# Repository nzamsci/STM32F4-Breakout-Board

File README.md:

# STM32F405RGT6 Microcontroller Breakout Board
[UNFINISHED] PCB Design based around the STM32F405RGT6 microcontroller. Design includes a 20-pin J-Link debug adapter (SWD), I2C, SPI, and USART interfaces, and a 16 MHz external oscillator.

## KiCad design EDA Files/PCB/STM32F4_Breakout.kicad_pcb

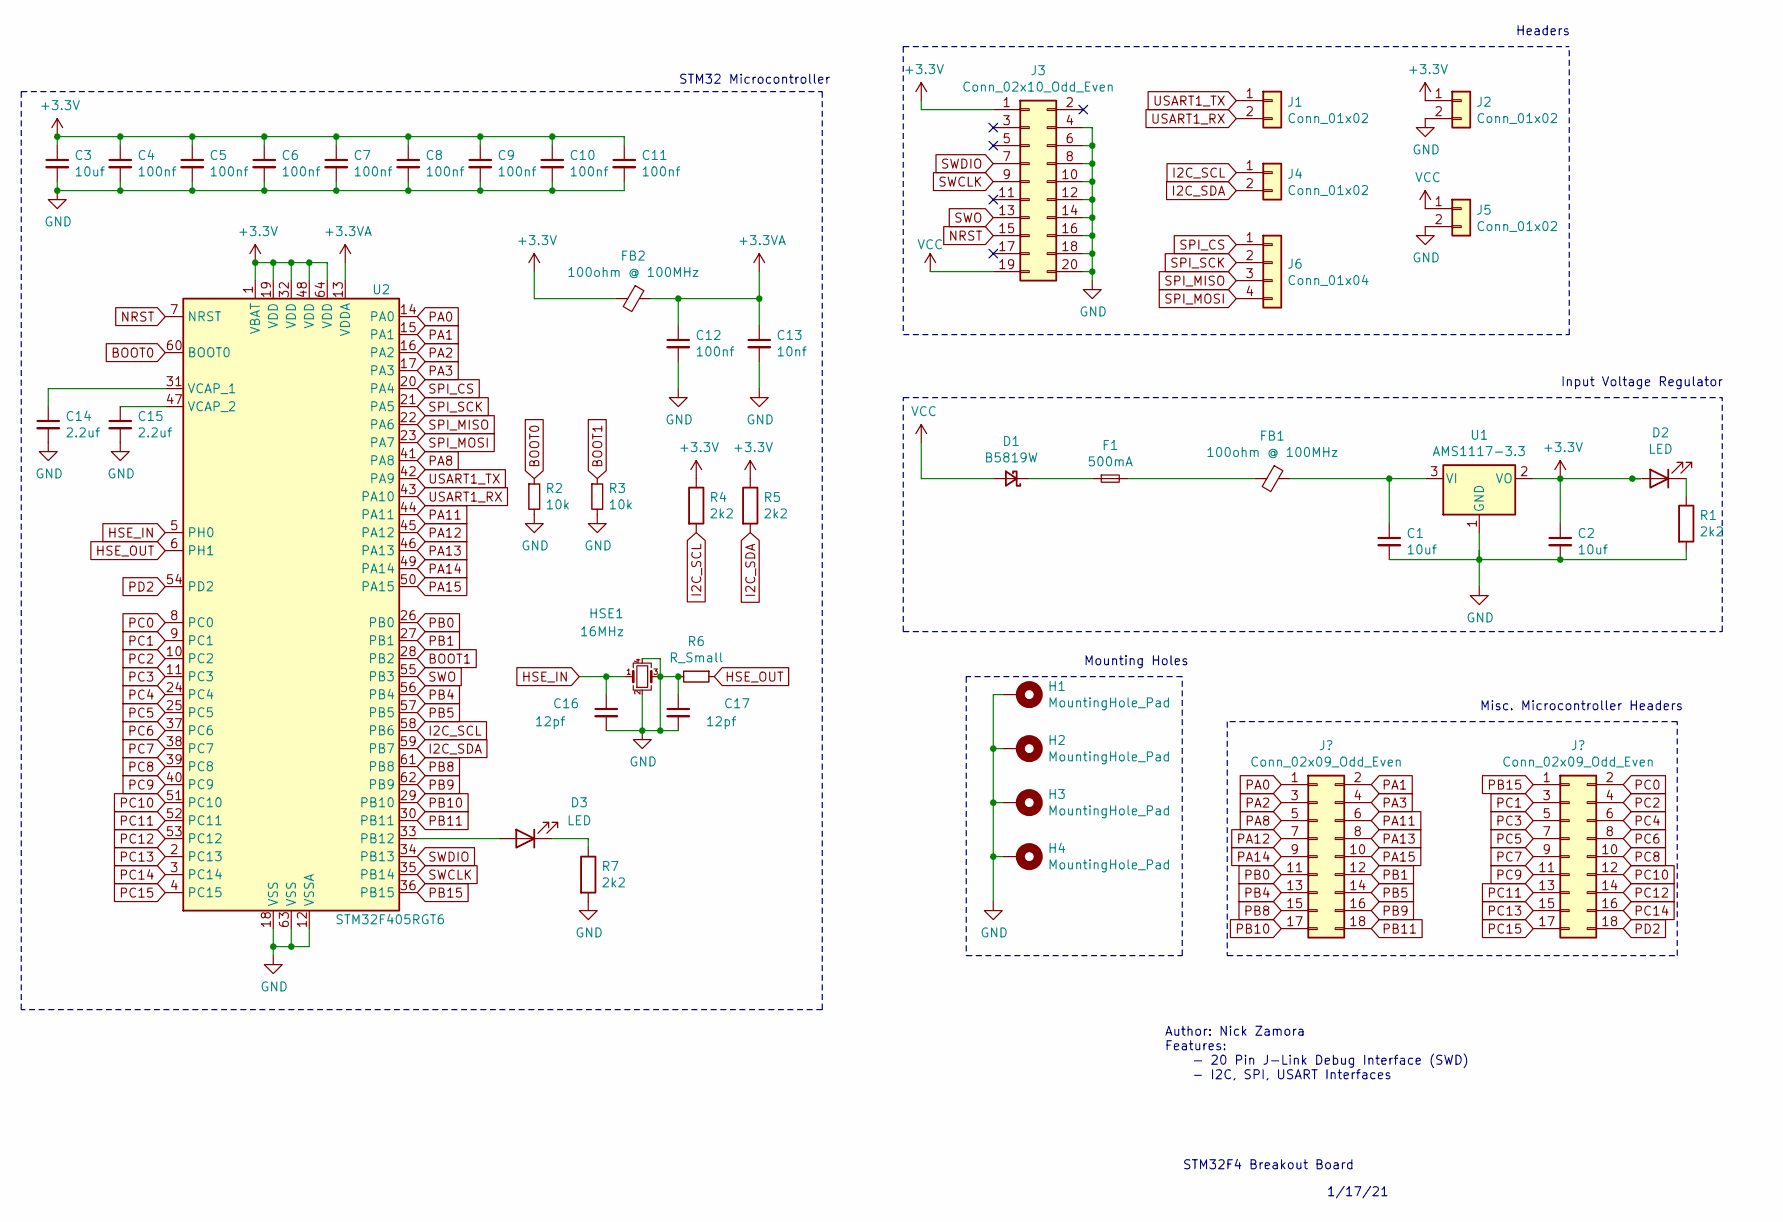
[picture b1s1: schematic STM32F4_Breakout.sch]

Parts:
C1, C2: 10uf; C_0805_2012Metric
C3: 10uf; C_0201_0603Metric
C4, C5, C6, C7, C8, C9, C10, C11, C12: 100nf; C_0402_1005Metric
C13: 10nf; C_0402_1005Metric
C14, C15: 2.2uf; C_0603_1608Metric
C16, C17: 12pf; C_0402_1005Metric
D1: B5819W; D_SOD-123
D2, D3: LED; LED_0603_1608Metric
F1: 500mA; Fuse_0603_1608Metric
FB1, FB2: 100ohm @ 100MHz; L_0805_2012Metric
H1, H2, H3, H4: MountingHole_Pad; MountingHole_4.3mm_M4_DIN965_Pad
HSE1: 16MHz; Crystal_SMD_3225-4Pin_3.2x2.5mm
J1, J2, J4, J5: Conn_01x02; PinHeader_1x02_P2.54mm_Vertical
J3: Conn_02x10_Odd_Even; PinHeader_2x10_P2.54mm_Vertical
J6: Conn_01x04; PinHeader_1x04_P2.54mm_Vertical
R1, R7: 2k2; R_0603_1608Metric
R2, R3: 10k; R_0402_1005Metric
R4, R5: 2k2; R_0402_1005Metric
R6: R_Small; R_0402_1005Metric
U1: AMS1117-3.3; SOT-223-3_TabPin2
U2: STM32F405RGT6; LQFP-64_10x10mm_P0.5mm

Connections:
+3.3VA: C12.1, C13.1, FB2.1, U2.13 (VDDA)
+3V3: C2.1, C3.1, C4.1, C5.1, C6.1, C7.1, C8.1, C9.1, C10.1, C11.1, D2.2 (A), FB2.2, J2.1, J3.1, R4.1, R5.1, U1.2 (VO), U2.1 (VBAT), U2.19 (VDD), U2.32 (VDD), U2.48 (VDD), U2.64 (VDD)
BOOT0: R2.1, U2.60 (BOOT0)
BOOT1: R3.1, U2.28 (PB2)
HSE_IN: C16.1, HSE1.1, U2.5 (PH0)
HSE_OUT: R6.1, U2.6 (PH1)
I2C_SCL: J4.1, R4.2, U2.58 (PB6)
I2C_SDA: J4.2, R5.2, U2.59 (PB7)
NRST: J3.15, U2.7 (NRST)
unnamed: C1.1, FB1.1, U1.3 (VI)
unnamed: C14.1, U2.31 (VCAP_1)
unnamed: C15.1, U2.47 (VCAP_2)
unnamed: D1.1 (K), F1.1
unnamed: D2.1 (K), R1.1
unnamed: D3.1 (K), R7.1
unnamed: D3.2 (A), U2.33 (PB12)
unnamed: F1.2, FB1.2
PA0: U2.14 (PA0)
PA1: U2.15 (PA1)
PA2: U2.16 (PA2)
PA3: U2.17 (PA3)
PA8: U2.41 (PA8)
PA11: U2.44 (PA11)
PA12: U2.45 (PA12)
PA13: U2.46 (PA13)
PA14: U2.49 (PA14)
PA15: U2.50 (PA15)
PB0: U2.26 (PB0)
PB1: U2.27 (PB1)
PB4: U2.56 (PB4)
PB5: U2.57 (PB5)
PB8: U2.61 (PB8)
PB9: U2.62 (PB9)
PB10: U2.29 (PB10)
PB11: U2.30 (PB11)
PB15: U2.36 (PB15)
PC0: U2.8 (PC0)
PC1: U2.9 (PC1)
PC2: U2.10 (PC2)
PC3: U2.11 (PC3)
PC4: U2.24 (PC4)
PC5: U2.25 (PC5)
PC6: U2.37 (PC6)
PC7: U2.38 (PC7)
PC8: U2.39 (PC8)
PC9: U2.40 (PC9)
PC10: U2.51 (PC10)
PC11: U2.52 (PC11)
PC12: U2.53 (PC12)
PC13: U2.2 (PC13)
PC14: U2.3 (PC14)
PC15: U2.4 (PC15)
PD2: U2.54 (PD2)
SPI_CS: J6.1, U2.20 (PA4)
SPI_MISO: J6.3, U2.22 (PA6)
SPI_MOSI: J6.4, U2.23 (PA7)
SPI_SCK: J6.2, U2.21 (PA5)
SWCLK: J3.9, U2.35 (PB14)
SWDIO: J3.7, U2.34 (PB13)
SWO: J3.13, U2.55 (PB3)
USART1_RX: J1.2, U2.43 (PA10)
USART1_TX: J1.1, U2.42 (PA9)
VCC: D1.2 (A), J3.19, J5.1

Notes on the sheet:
Input Voltage Regulator
STM32 Microcontroller
Mounting Holes
Headers
STM32F4 Breakout Board
Author: Nick Zamora Features: - 20 Pin J-Link Debug Interface (SWD) - I2C, SPI, USART Interfaces
1/17/21
Misc. Microcontroller Headers

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
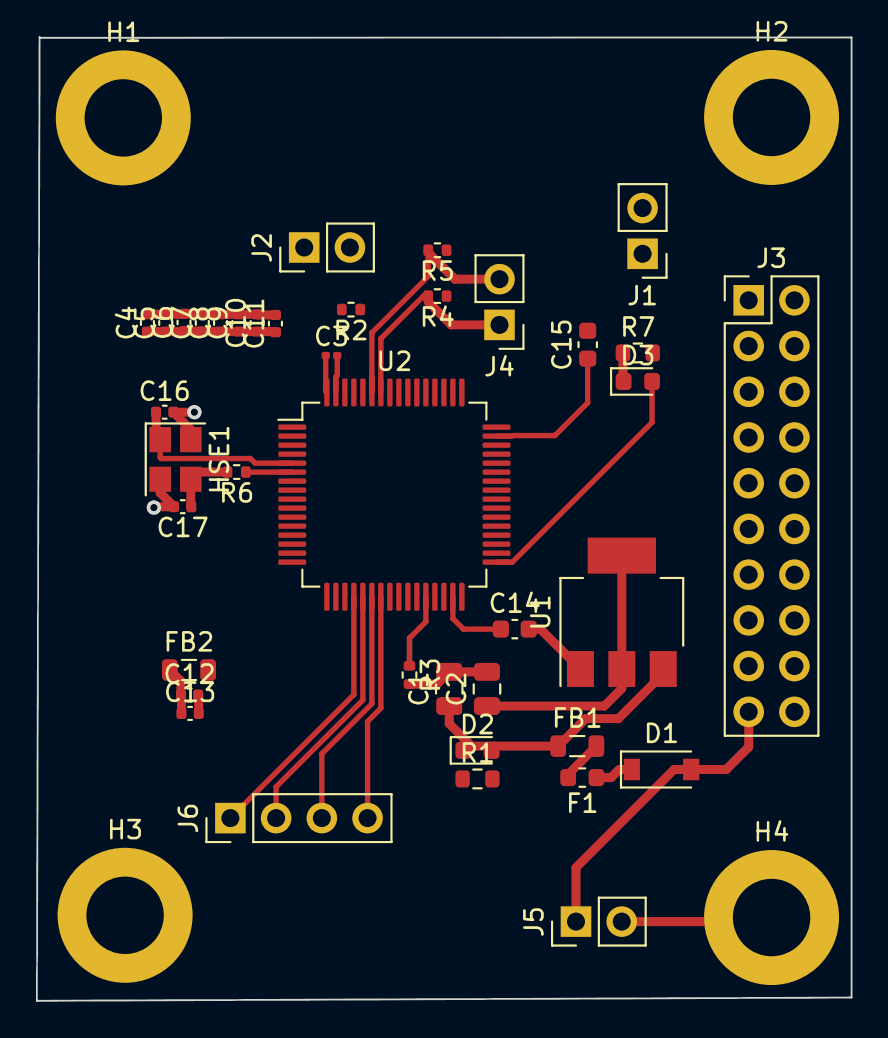
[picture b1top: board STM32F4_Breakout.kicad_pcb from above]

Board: 4 copper layers, 45.3 x 53.5 mm, 43 parts (0 on the bottom side), 29 nets.

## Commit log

2021-01-23 Added Schematic
2021-01-23 Updated PCB
2021-01-23 Updated Schematic
2021-01-23 Added Image
